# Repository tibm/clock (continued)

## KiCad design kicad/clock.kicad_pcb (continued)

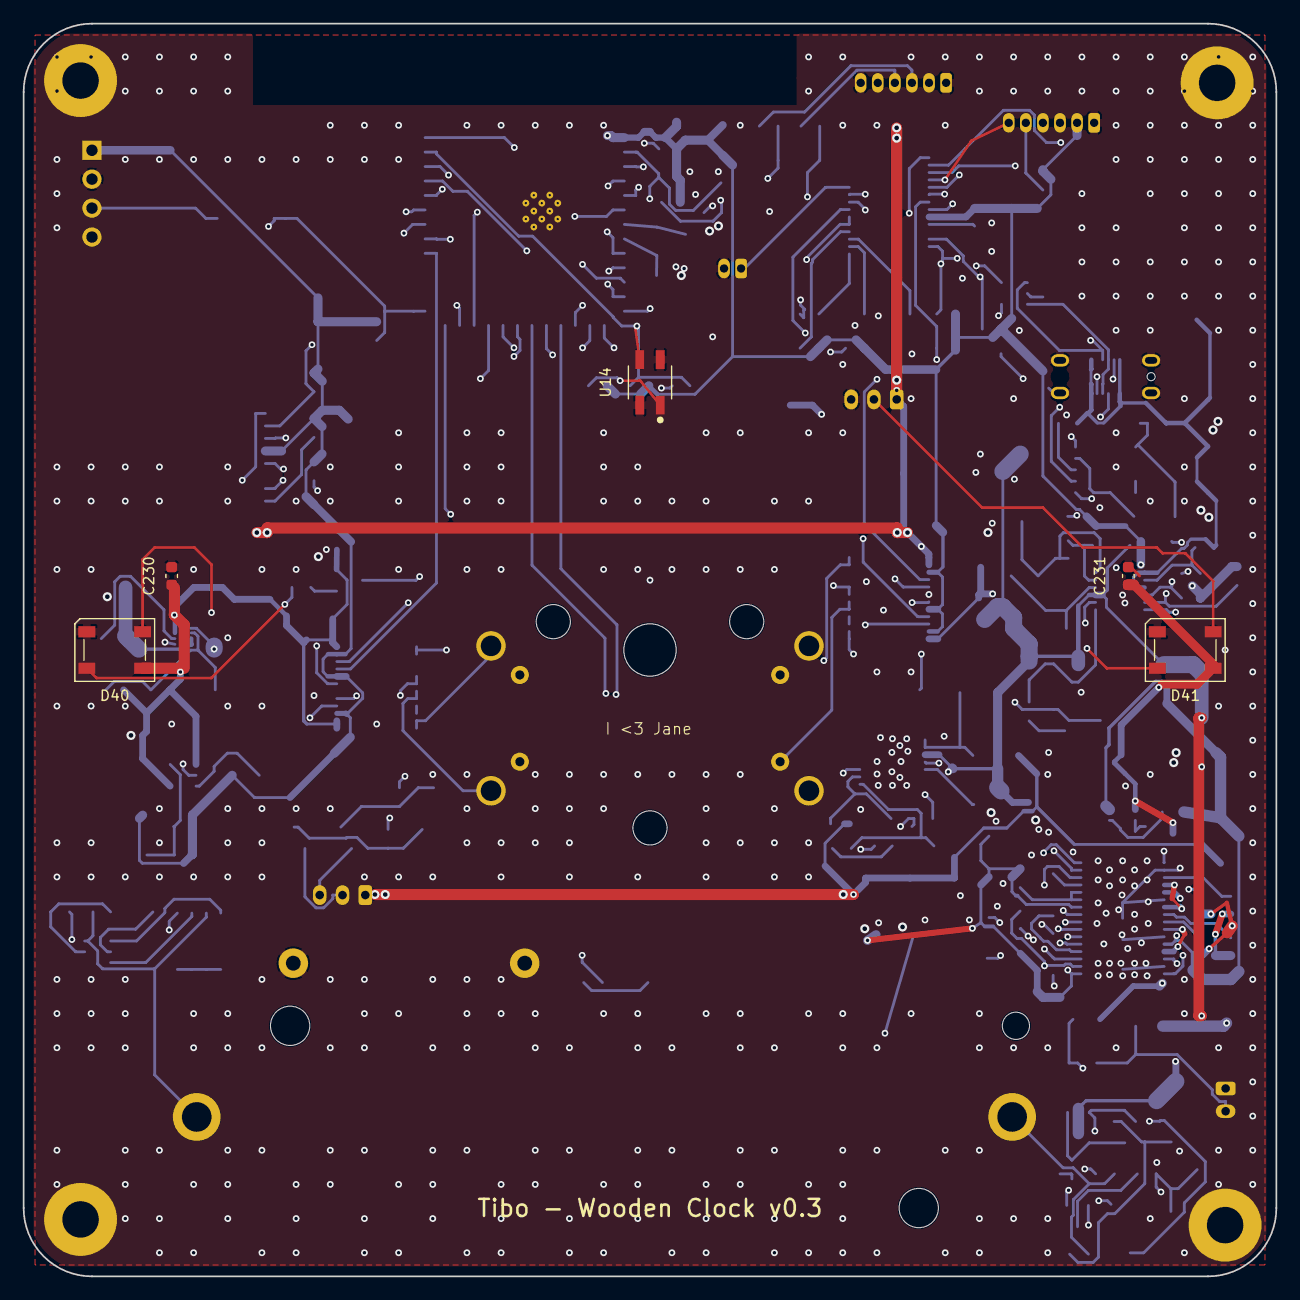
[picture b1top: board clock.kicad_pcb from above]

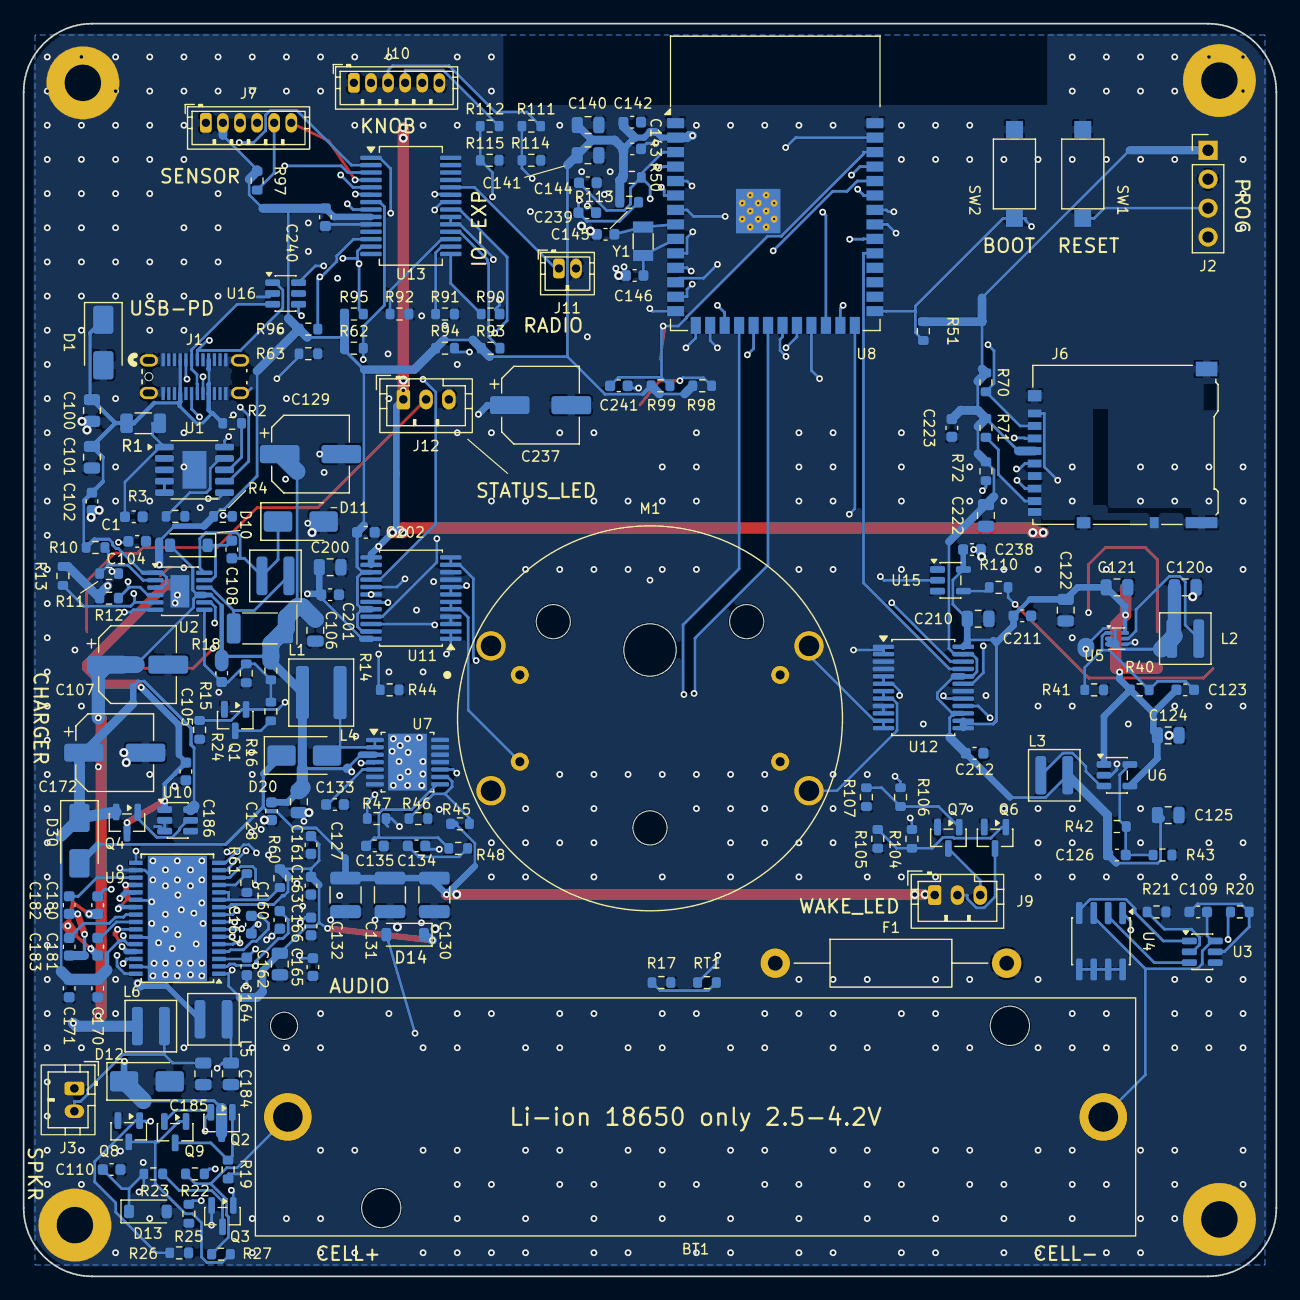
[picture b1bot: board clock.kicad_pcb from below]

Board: 4 copper layers, 110.0 x 110.0 mm, 187 parts (178 on the bottom side), 131 nets.

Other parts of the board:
H1, H2, H3, H4: MountingHole_3.2mm_M3_Pad

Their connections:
GND: H1.1, H2.1, H3.1, H4.1; also elsewhere on the board

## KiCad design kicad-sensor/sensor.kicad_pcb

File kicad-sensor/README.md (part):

# Wooden Smart Clock — sensor board (KiCad)

Small SMT daughterboard carrying the three off-board sensors, plugged into
**main-board J7** on a 6-way JST ZH harness. Open `sensor.kicad_pro`.

**The schematic is generated** by the Python in `gen/` (see *Regenerating*) —
edit the block files, not the `.kicad_sch`. **The PCB is not**: it has been
hand-placed and hand-routed since 2026-08-02, so `gen/pcb_build.py` refuses to
run and board changes are made in pcbnew + *Update PCB from Schematic* (F8).

**PCB: 30 × 16 mm, 4 layers, 1.6 mm — fully routed, `SENSE v0.2`
(2026-08-07).** Front face = the two sensors that must see the outside world
(TSL2591 window + BME688 vent); back face = the harness connector and the IMU.
Full rationale, floor plan, verification and the list of accepted deviations
in [`PCB_NOTES.md`](PCB_NOTES.md); the design review that drove v0.2 is in
[`REVIEW.md`](REVIEW.md).

This is "option **2b**" of [`../datasheet/README.md`](../datasheet/README.md) §15:
the same sensor set as the STEMMA-QT bring-up chain, on one board, at the same
I²C addresses, so firmware written against the breakouts runs unchanged.

| Ref | Part | Package | I²C | Datasheet |
|---|---|---|---|---|
| U1 | **BNO085** (CEVA/Hillcrest 9-axis fusion IMU, SH-2 on-chip) | LGA-28 5.2×3.8 *(land in `sensor.pretty`)* | **0x4A** (R3) / 0x4B (R4) | `../datasheet/sensor_imu_bno085.pdf` |
| U2 | **BME688** (gas/VOC + RH + pressure + temp) | LGA-8 3×3 | **0x77** (R10) / 0x76 (R11) | `../datasheet/sensor_env_bme688.pdf` + `…_bme68x_hsmi.pdf` |
| U3 | **TSL2591** (`TSL25911FN`, 188 µlx–88 klx ALS) | DFN-6 2×2 *(land in `sensor.pretty`)* | **0x29** (fixed) | `../datasheet/sensor_light_tsl2591.pdf` |
| Y1 | ABS07-32.768KHZ-T (BNO085 clock) | 3.2×1.5 SMD | — | `../datasheet/xtal_32k_abs07.pdf` |
| J1 | JST ZH **B6B-ZR** 1×06 | TH vertical | — | `../datasheet/connector_jst_zh.pdf` |

**Address straps are 10 kΩ, not 0 Ω** (v0.2). Exactly one of each pair is
fitted; the alternate carries a real `DNP` flag. Fitting both halves is the
assembly slip this layout invites, and through 0 Ω it would short the **main
board's** +3V3 rail to GND — on a daughterboard with no LED and no silk hint,
which is hours of debugging. Through 10 k the same slip costs 330 µA, the
clock still boots, and the part answers at a wrong-but-visible address.

No clash with the main board's own I²C devices (MCP23017 **0x20**, TAS5760M
**0x6C** — `SLEEP/ADR` strapped to GND, `kicad/gen/b_audio.py`; 0x6D is the
ADR-high alternate).

## J1 pinout — mirrors main-board J7 **1:1**

| Pin | Net | Main board (J7) | Sensor board |
|---|---|---|---|
| 1 | `GND` | GND | GND |
| 2 | `+3V3` | +3V3 | rails in — no regulator on this board |
| 3 | `I2C_SDA` | shared bus (4.7 k PU = R95) | U1.20 · U2.3 · U3.6 (+ R1 10 k) |
| 4 | `I2C_SCL` | shared bus (4.7 k PU = R96) | U1.19 · U2.4 · U3.1 (+ R2 10 k) |
| 5 | `SENSOR_INT` | MCU **IO42** IRQ, 10 k PU = R97 | **U1.14 `H_INTN` only** (push-pull, active low) |
| 6 | `ALS_INT` | **MCP23017 GPB3** (U13.4) | **U3.2 `INT`** (open drain, R12 10 k PU here — the only one on the net) |

Pin 6 was a spare wire when this board was designed; `kicad/REVIEW.md` #11
landed it on expander **GPB3**, so the ALS interrupt is live. Because the
pull-up lives only here, firmware must also set **`GPPU.3 = 1`** so GPB3 does
not float when this board is unplugged — `FIRMWARE.md` **R-BOARD-4**.

### ⚠ Harness polarity is a destructive fault

Both ends are ZHR-6 on the same pre-crimped cable and J1 mirrors J7 1:1, so a
cable loaded **backwards plugs in perfectly** — and J1.5 then receives J7.2
**+3V3 while this board's VDDIO is 0 V**. BNO08X abs max (Fig. 6-1) is
*"VDDIO + 0.3 V at any logic pin"*, series-limited only by the main board's
R97 10 k: **assume U1 ($13.57, the most expensive part on either board) is
destroyed.**

**This is not a hypothetical, and it is not only a mis-crimp: JST sells the
backwards cable as a catalogue part.** `A06ZR06ZR28H152`**`A`** is the
*Reversed* build (pin 1 ↔ pin 6, DigiKey 455-3027-ND) and
`A06ZR06ZR28H152`**`B`** is straight through (pin 1 ↔ pin 1, DigiKey
455-3039-ND) — one character apart, indistinguishable in the bag. The BOM has
always said `…B`; the cable that arrived for build #1 on **2026-09-08** was an
`…A`, and a continuity check is the only reason U1 survived it.

> **Standing procedure, before this harness ever goes into a powered board:**
> DMM on continuity, cable out of both boards, **pin 1 of one end to pin 1 of
> the other**. A beep on pin 1 ↔ pin 6 instead means re-pin it or bin it.

Worse, the main board's **J10** (knob) is the *same* ZH 1×06 header **13.5 mm
from J7**, with **+5 V on pin 2** — that mis-mate puts 5 V on `+3V3` and takes
out all three sensors at once (abs max: BNO085 VDDIO 3.63 V, TSL2591 3.8 V,
BME688 4.25 V).

Neither is keyed out, and **the connector is not going to change** — a 1×07
was proposed and rejected on 2026-08-08 ([`REVIEW.md`](REVIEW.md)). The guard
is marking, and it has to be followed: the main board carries **`SENSOR` and
`KNOB` on B.Silk** beside J7 and J10, so **label both harnesses to match, and
check the cable before first power-up.** The reversed-cable warning is also
printed on the schematic sheet next to J1 and on J10's BOM line, so it is in
front of whoever assembles the clock rather than only in this file.

## Design notes (all traceable to a datasheet line)

**BNO085 (`gen/b_imu.py`)** — follows the CEVA I²C reference design
(Fig. 1-11 and its notes 1-8):
- `PS1 = PS0 = 0` → I²C; `BOOTN` 10 k pull-up (R7) with test pad TP2 — pull it
  low at reset for the DFU bootloader.
- `CAP` (pin 9) → 100 nF to GND; VDD and VDDIO each get their own 100 nF
  (C3/C4) plus a 1 µF local bulk (C5) the reference omits — this board hangs
  off a long harness.
- **VDD and VDDIO share the 3V3 rail.** §6.3 demands VDD reach level *before
  or with* VDDIO; one rail satisfies that by construction.
- **32.768 kHz crystal** (Y1 + C7/C8 22 pF) with `CLKSEL0` **tied straight to
  GND — a bare wire, no strap resistor** (Fig. 1-8: *"0 or unconnected"*
  selects the crystal). The performance table (Fig. 6-14) is specified *only*
  for an external clock or crystal, so the internal RC is not used. Same ABS07
  part as the main board's RTC crystal (12.5 pF CL, ±20 ppm; CEVA asks
  50 ppm/12.5 pF).
- **`ENV_SCL`/`ENV_SDA` (pins 15/16) are pulled up although unused** — note 8:
  the SH-2 firmware probes that secondary bus at every reset. They are *not*
  tied to the host bus; on that bus the BNO085 is the master.
- **`NRST`**: J7 has no spare host line, so R6/C9 form a 10 k/100 nF power-on
  reset (TP1 to drive it by hand). It also guarantees the reset-sampled straps
  (BOOTN, PS1, PS0, CLKSEL0) are settled before release.
- **Deviation:** pin 18 `H_CSN` is unused in I²C mode and Fig. 1-11 leaves it
  open; R5 pulls it to VDDIO instead, so no CMOS input floats on a battery
  product. Harmless in every mode — `H_CSN` is not sampled at reset.

**BME688 (`gen/b_env.py`)** — §7.2 connection diagram (a):
- **`CSB` hard-tied to VDDIO.** §6.1: pull CSB low even once and the part
  latches into SPI until the next power-on reset and never answers I²C again.
- `SDO` must not float (§6.2). R10 (**10 k**) fitted → 0x77, matching the
  Adafruit 5046 breakout used for bring-up — which also uses 10 k; R11 (DNP)
  → 0x76, Bosch's own default. `SDO` is address-select only in I²C mode
  (Table 26) and is never driven, so a resistive strap is unambiguous.
- 100 nF on each supply (C10/C11).
- **Handling is the risk on this part, not wiring** — see *Assembly* below.

**TSL2591 (`gen/b_als.py`)** — "Application Information":
- **1 µF low-ESR at VDD** (C12), placed as close as possible to the pin.
- `INT` is open-drain → R12 10 k. Pin 4 is "NC — do not connect".

**Board level (`gen/b_host.py`)** — C1 10 µF + C2 100 nF at the connector
absorb the BME688 heater bursts (~18 mA peak) and the BNO085 turn-on so they
do not ride back up the single power wire. R1/R2 10 k parallel the main
board's 4.7 k to ≈3.2 k, inside the 2–4 kΩ window CEVA asks for (note 7) and
fast enough for 400 kHz over the harness; depopulate both to run on the 4.7 k
alone at 100 kHz. Two PWR_FLAGs declare the rails to ERC — nothing on this
board drives them.

## ⚠ Firmware constraint — do not poll the BNO085

Poll a BNO085 that has no data ready and it **stretches SCL until it does**
(§1.2.2.1). On this shared bus that stalls the BME688, the TSL2591 *and* the
main board's MCP23017 (knob, charger status, amp shutdown). Read it **only
after `SENSOR_INT` asserts**. `SENSOR_INT` carries nothing else, which is why
the TSL2591's interrupt went to the spare pin 6 instead.

Second, related, main-board item: CEVA says `H_INTN` "should be tied to a GPIO
**with wake capability**". `SENSOR_INT` lands on **IO42** (`../esp32.md`), which
is *not* an ESP32-S3 RTC GPIO (only IO0–IO21 are), so it can wake light sleep
but **not** `ext0`/`ext1` deep sleep. Fine if the clock never deep-sleeps with
tap-to-wake armed; otherwise move `SENSOR_INT` to an RTC-capable pin on the
next main-board revision. Not changed here — this board only presents the
signal on J1.5.

## Assembly

**All three sensors are leadless** (LGA-28 / LGA-8 / DFN-6) — this board
**cannot** be hand-soldered with an iron. Order it **fab-assembled**, or
reflow it yourself with a stencil + hotplate. The main board's
hand-solderable-only rule scopes the main PCB; this daughterboard is the
escape hatch that rule always assumed (`../datasheet/README.md` §15, path 2b).

**J1 is the only through-hole part**, so the board actually needs **three**
operations: reflow side 1, reflow side 2, then selective- or hand-solder J1.
Price that before committing — it is usually quoted per board, not per joint.
`B6B-ZR-SM4-TF` (same ZHR-6 housing, SMT with brass reinforcement) would
remove it at the cost of pull-out strength.

### ⚠ BME688 (U2) — put these in the fab package

A metal-oxide gas hotplate does not *fail* when mishandled; it reads a wrong
VOC baseline for ever, and a correctly-executed routine assembly process is
enough to do it. Datasheet §7.7 defers every rule to a separate **HSMI**
document, and Bosch publishes no BME688-specific one (checked 2026-08-07), so
the BME680 HSMI is filed as nearest-applicable — same LGA-8 3×3 package, same
Ø0.35 mm lid vent, same MOX element: **`../datasheet/sensor_env_bme68x_hsmi.pdf`**
(+ `…_bme68x_packaging.pdf`).

**These rules are in `U2`'s `Notes` field**, so they travel with the exported
BOM CSV to the assembly house instead of living only here — an assembler who
never opens this repo still gets them on the line they are quoting. Send
`../datasheet/sensor_env_bme68x_hsmi.pdf` with the fab package and get the
≥ 50 µm solder height agreed **before** the run: it is a stencil-thickness
decision, not something that can be fixed afterwards.

| Rule | |
|---|---|
| **MSL 1** | no bake needed |
| **Peak reflow 260 °C, 20–40 s**, **≤ 3 cycles** | this board is double-sided, so U2 already sees two |
| **≥ 50 µm solder height after reflow** | a **stencil-thickness** decision, not a layout one — it is what mechanically decouples the die from the board |
| **Cover the vent** with a silicone-free layer for any cleaning / board wash | or specify no-clean and no wash |
| **No siloxanes** — coatings, adhesives, gloves, packaging | permanent VOC poisoning |
| No conformal coat, no underfill, no ultrasonic welding, nothing sharp in the vent, no rear-side handling | |

## Custom footprints (`sensor.pretty`, fp-lib-table nickname `sensor`)

| Footprint | Part | Source |
|---|---|---|
| `AMS_TSL25911FN_ALSWindow` | U3 | **Fork of stock `OptoDevice:AMS_TSL25911FN`** (v0.2). Identical pads, courtyard, F.Fab and Cmts.User; the **F.Silk package outline is removed** and the pin-1 marker moved outboard. The stock silk crosses the enclosure's Ø4.0 mm optical window 1.31 mm from the photodiode, and white silk that close under a window is a diffuse reflector. Forked rather than hand-edited on the board so *Update Footprints from Library* cannot put it back — and so `kicad-cli pcb drc` stays at 0 (a hand-edited instance reports `lib_footprint_mismatch` for ever). Its `(model …)` points straight at `3d/AMS_TSL25911FN.step`, the override the stock footprint needed anyway. |
| `CEVA_BNO085_LGA-28_5.2x3.8mm_P0.5mm` | U1 | **Vendor (SnapEDA) land, verified against BNO08X datasheet Fig. 7-2** — measured land extents **5.2000 × 3.8000 mm**, i.e. exactly the drawing. Pad centres ±1.5625 (10-pad rows) and ±2.3125 (4-pad ends), pads 0.25 × 0.675 / 0.575 × 0.25. Cleaned on import: SnapEDA's per-pad `solder_mask_margin 0.102` **removed** (at 0.5 mm pitch it left a 0.046 mm mask web — below any fab's minimum dam, so the mask would have silently ganged; board default gives 0.25 mm), pin-1 silk dot grown from Ø0.2 to Ø0.42 (was under the 0.15 mm silk minimum), `3d/BNO085.step` linked, renamed to house style, resaved through `kicad-cli fp upgrade`. Pad numbering/arrangement cross-checked against the drawing and against KiCad's stock generic pattern — identical. |

KiCad's stock `Package_LGA:LGA-28_5.2x3.8mm_P0.5mm` is a **generic IPC** land: same
numbering and arrangement, but ~0.10 mm (row pads) / 0.125 mm (end pads) of extra toe
per side → 4.00 × 5.45 instead of 3.80 × 5.20. Not wrong, just unverified against this
part; the vendor land above is used instead so nothing needs checking before fab.

## Custom symbol (`gen/sensor_custom.kicad_sym`)

`BNO085` — KiCad has no BNO08x symbol (`Sensor_Motion:BNO055` is the same
*package* with a completely different pinout). Pins are grouped by function:
host I²C and the strapped pins on the left, clock / CAP / ENV bus on the
right, supplies top, grounds bottom, and the nine `RESV_NC` pads kept visible
so every pad is accounted for. The other two sensors use stock symbols
verbatim — `Sensor:BME680` with the value overridden to **BME688** (identical
pin table per BME688 Table 26 and identical LGA-8 3×3 P0.8 clockwise package)
and `Sensor_Optical:TSL25911FN`.

## Before fab

1. ~~LGA-28 land pattern~~ — **closed 2026-07-29**: U1 now uses the vendor land in
   `sensor.pretty`, measured against datasheet Fig. 7-2 (see above). The BME688
   (`Bosch_LGA-8_3x3mm_P0.8mm_ClockwisePinNumbering`) and TSL2591 (stock
   `OptoDevice:AMS_TSL25911FN`, forked here only to trim its silk) footprints
   are part-specific KiCad libs generated from those datasheets, so they need
   no separate check.
2. **Harness polarity** — 1:1, not reversed. Label both cables; J10 on the
   main board is the same connector 13.5 mm away (above).
3. ~~Placement~~ — **closed 2026-07-30**, revised 2026-08-07, see
   [`PCB_NOTES.md`](PCB_NOTES.md): U2 has the far corner, a 4-layer pour
   keepout, a clear back side and a Ø5.2 mm vent marked on `User.Drawings`; U3
   has a Ø4.0 mm window with nothing but its own pads inside it, on copper or
   silk; U1 sits 0.038 mm off the line between the two M2 screws. Still on the
   enclosure side: keep the vent away from the amp/LED/battery heat and the
   ALS off-axis from the dial LEDs, and **use nylon or brass M2 screws** —
   steel next to the magnetometer is a permanent hard-iron offset.
4. ~~Route it~~ — **closed 2026-08-02**: 193 segments, 30 vias, 4 GND pours.
5. **BME688 handling** — the HSMI rules above go in the fab package with the
   Gerbers, and the ≥ 50 µm solder height is a stencil decision the assembler
   has to agree to *before* the run.

## Validation (2026-08-07, v0.2)

- `kicad-cli sch erc sensor.kicad_sch` → **0 violations**, and *"Global label
  only appears once in the schematic"* is **no longer suppressed** — on a
  single-sheet design where every inter-block connection is a global label,
  that is the check that catches a typo'd label name.
- `kicad-cli pcb drc --severity-all` → **0 violations, 0 unconnected items, 0
  schematic-parity issues.**
- `gen/pcb_check.py`, which re-checks the *saved* file independently (loads the
  board, re-exports the netlist, re-derives the outline from Edge.Cuts) →
  **33/33**. It was re-baselined for v0.2: it now judges part clearance on
  **pad-to-pad copper** (≥ 0.60 mm everywhere) rather than on courtyards,
  checks mounting holes at the **hole wall** rather than at the screw-head
  keepout, and adds three checks — every filled zone island is stitched, no
  F.Silk inside the optical window, and **PCB title block == schematic title
  block == the `SENSE v0.2` silk legend**. Details in
  [`PCB_NOTES.md`](PCB_NOTES.md).
- BOM: all 29 BOM parts carry MPN/Manufacturer/Package/Description, board
  fields identical to the schematic's, and the DNP / off-BOM sets agree
  between the two files. `gen/stamp_bom.py` re-run is a no-op (idempotent) and
  both files round-trip byte-identically through KiCad's own writers.
- `gen/build.py` lint: no dangling wires, no body overlaps, no wires through
  symbols; junctions placed by eeschema's own rules so a GUI re-save is a
  no-op. The sheet is normalised through `kicad-cli sch upgrade`, so opening
  and saving in eeschema produces zero diff.
- Netlist spot-checked pin-by-pin against the three datasheets (every
  `RESV_NC` and the TSL2591 `NC` land on their own unconnected nets).

## BOM part data (`gen/parts_db.py` + `gen/stamp_bom.py`, 2026-08-01)

The generators only emit Value + Footprint, which is not a BOM: this board is
**ordered fab-assembled**, so every line has to be unambiguous to an assembly
house (`MPN` + `Package`) and the parts that must *not* be fitted have to say
so in a field, not in a value string.

```
cd gen && python3 stamp_bom.py          # --dry-run to preview
```

splices **MPN / Manufacturer / Package / Description / Notes** into *both*
`sensor.kicad_sch` (eeschema + `kicad-cli` BOMs) and `sensor.kicad_pcb` (the
PCBWay plug-in reads *footprint* fields) — in place, no regeneration, so hand
DRC fixes survive — then sets two kinds of flag and hands both files back to
KiCad's own serializers (`kicad-cli sch upgrade` + `gen/pcb_canon.py`) so they
stay byte-identical to a GUI save. Idempotent; fails loudly on a part that is
missing from the db. **Re-run it after every `build.py` rebuild** — the
schematic generator writes its file from scratch and drops the fields.

- **DNP** (`parts_db.DNP`) → `(dnp yes)` on the symbol + the `dnp` footprint
  attribute. **R4 and R11 are the alternate I²C-address straps**: only their
  *value strings* said "(DNP)", so a BOM taken before 2026-08-01 told the
  assembler to fit them — and R3+R4 or R10+R11 fitted together tied +3V3 to
  GND through 0 Ω. They now export with KiCad's `DNP` column set **and** the
  straps are **10 k** (v0.2), so the flag is the guard and the value is the
  fail-safe under it: the same slip now costs 330 µA instead of the main
  board's 3.3 V rail.
- **Not a part** (`parts_db.EXCLUDE_FROM_BOM`) → `(in_bom no)` +
  `(in_pos_files no)` on TP1/TP2, matching the `exclude_from_bom` their
  footprints already carried, so the schematic-side and PCB-side BOMs agree
  (and "Update PCB from Schematic" can't put the test pads back).

Part data: the three sensors + the crystal + J1 are local to
`gen/parts_db.py`; the **generic passives are imported from the main board's
`../../kicad/gen/parts_db.py`**, so both boards order the same physical 0603 /
0805 parts. Per-reference data never falls through to the main board's table —
J1/U1/U2/U3/Y1 exist there too and mean different parts. DigiKey status/price
re-verified 2026-08-01 (BNO085 1888-1006-1-ND $13.57 · BME688 828-BME688CT-ND
$8.99 — `../datasheet/README.md` §12's ~$5 is the reel price · TSL25911FN
TSL25911FNTR-ND $1.74; all Active) and J1 re-checked 2026-08-07
(455-B6B-ZR-ND, $0.24, 9,478 pcs).

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
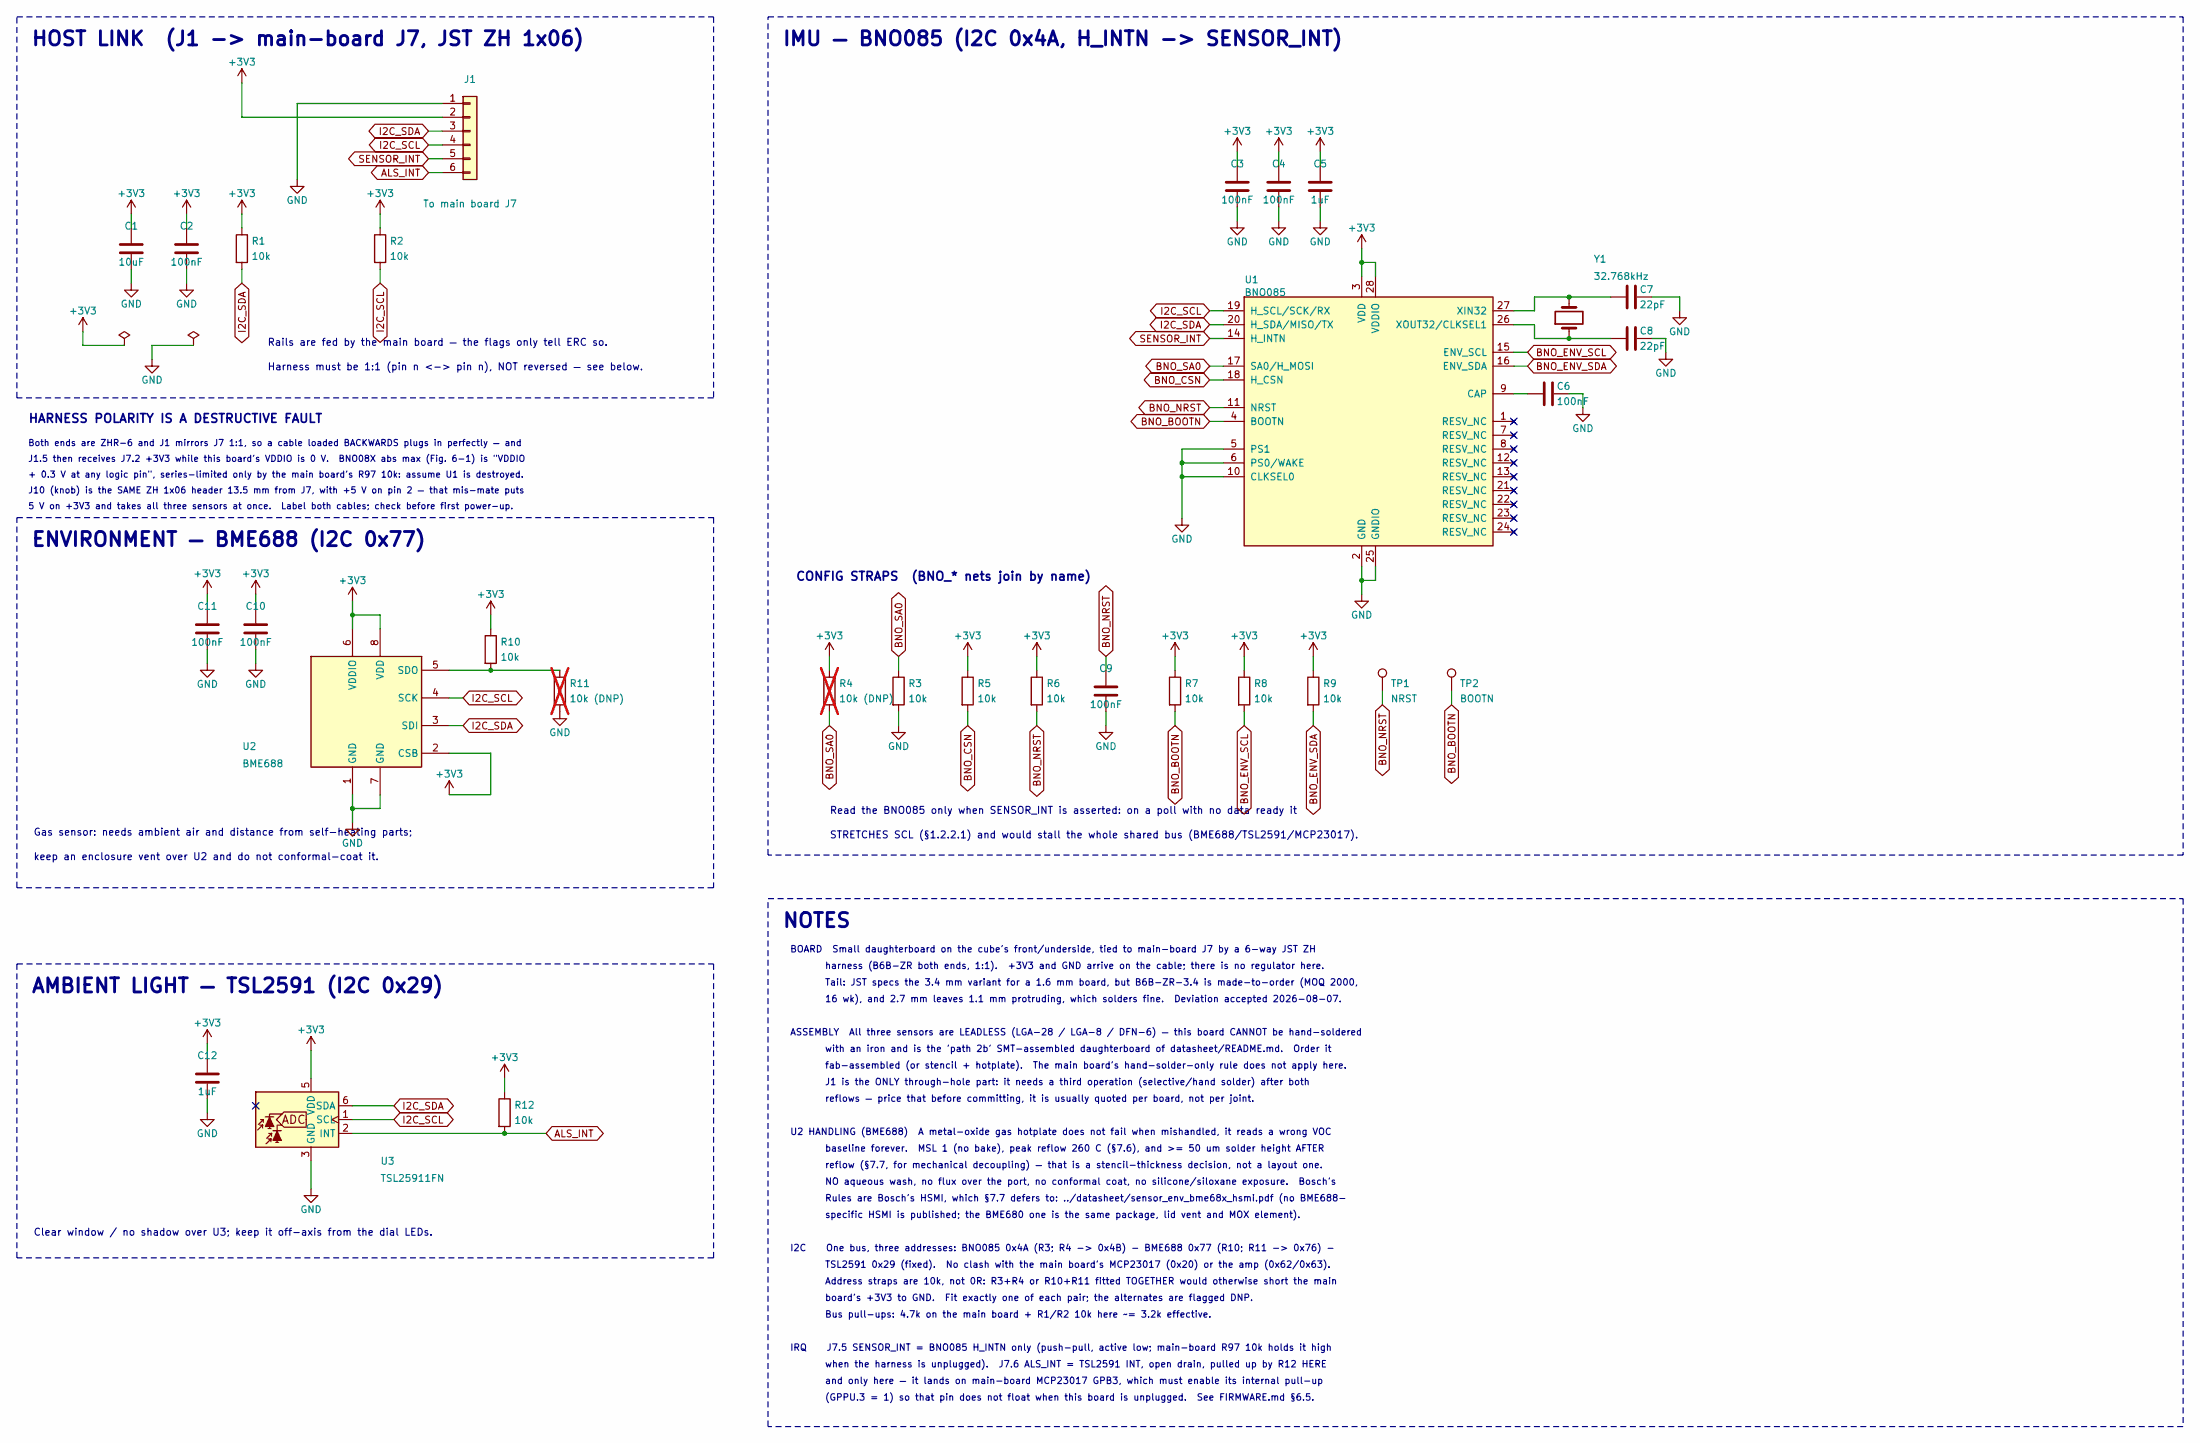
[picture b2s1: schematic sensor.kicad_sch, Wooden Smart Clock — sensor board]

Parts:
C1: 10uF; C_0805_2012Metric; MPN CL21A106KAYNNNE
C2, C3, C4, C6, C9, C10, C11: 100nF; C_0603_1608Metric; MPN CL10B104KB8NNNC
C5, C12: 1uF; C_0603_1608Metric; MPN CL10B105KA8NNNC
C7, C8: 22pF; C_0603_1608Metric; MPN CL10C220JB8NNNC
J1: To main board J7; JST_ZH_B6B-ZR_1x06_P1.50mm_Vertical; MPN B6B-ZR(LF)(SN)
R1, R2, R3, R5, R6, R7, R8, R9, R10, R12: 10k; R_0603_1608Metric; MPN RC0603FR-0710KL
R4, R11: 10k (DNP); R_0603_1608Metric; MPN RC0603FR-0710KL; not fitted
TP1: NRST; TestPoint_Pad_D1.0mm
TP2: BOOTN; TestPoint_Pad_D1.0mm
U1: BNO085; CEVA_BNO085_LGA-28_5.2x3.8mm_P0.5mm; MPN BNO085
U2: BME688; Bosch_LGA-8_3x3mm_P0.8mm_ClockwisePinNumbering; MPN BME688
U3: TSL25911FN; AMS_TSL25911FN_ALSWindow; MPN TSL25911FN
Y1: 32.768kHz; Crystal_SMD_3215-2Pin_3.2x1.5mm; MPN ABS07-32.768KHZ-T

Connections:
+3V3: C1.1, C2.1, C3.1, C4.1, C5.1, C10.1, C11.1, C12.1, J1.2, R1.1, R2.1, R4.1, R5.1, R6.1, R7.1, R8.1, R9.1, R10.1, R12.1, U1.3 (VDD), U1.28 (VDDIO), U2.2 (CSB), U2.6 (VDDIO), U2.8 (VDD), U3.5 (VDD)
ALS_INT: J1.6, R12.2, U3.2 (INT)
BNO_BOOTN: R7.2, TP2.1, U1.4 (BOOTN)
BNO_CSN: R5.2, U1.18 (H_CSN)
BNO_ENV_SCL: R8.2, U1.15 (ENV_SCL)
BNO_ENV_SDA: R9.2, U1.16 (ENV_SDA)
BNO_NRST: C9.1, R6.2, TP1.1, U1.11 (NRST)
BNO_SA0: R3.1, R4.2, U1.17 (SA0/H_MOSI)
GND: C1.2, C2.2, C3.2, C4.2, C5.2, C6.2, C7.2, C8.2, C9.2, C10.2, C11.2, C12.2, J1.1, R3.2, R11.2, U1.2 (GND), U1.5 (PS1), U1.6 (PS0/WAKE), U1.10 (CLKSEL0), U1.25 (GNDIO), U2.1 (GND), U2.7 (GND), U3.3 (GND)
I2C_SCL: J1.4, R2.2, U1.19 (H_SCL/SCK/RX), U2.4 (SCK), U3.1 (SCL)
I2C_SDA: J1.3, R1.2, U1.20 (H_SDA/MISO/TX), U2.3 (SDI), U3.6 (SDA)
unnamed: C6.1, U1.9 (CAP)
unnamed: C7.1, U1.27 (XIN32), Y1.2
unnamed: C8.1, U1.26 (XOUT32/CLKSEL1), Y1.1
unnamed: R10.2, R11.1, U2.5 (SDO)
SENSOR_INT: J1.5, U1.14 (H_INTN)

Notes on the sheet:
STRETCHES SCL (§1.2.2.1) and would stall the whole shared bus (BME688/TSL2591/MCP23017).
ENVIRONMENT — BME688 (I2C 0x77)
Rails are fed by the main board — the flags only tell ERC so.
J1.5 then receives J7.2 +3V3 while this board's VDDIO is 0 V. BNO08X abs max (Fig. 6-1) is "VDDIO
Rules are Bosch's HSMI, which §7.7 defers to: ../datasheet/sensor_env_bme68x_hsmi.pdf (no BME688-
ASSEMBLY All three sensors are LEADLESS (LGA-28 / LGA-8 / DFN-6) — this board CANNOT be hand-soldered
reflows — price that before committing, it is usually quoted per board, not per joint.
fab-assembled (or stencil + hotplate). The main board's hand-solder-only rule does not apply here.
5 V on +3V3 and takes all three sensors at once. Label both cables; check before first power-up.
BOARD Small daughterboard on the cube's front/underside, tied to main-board J7 by a 6-way JST ZH
HARNESS POLARITY IS A DESTRUCTIVE FAULT
baseline forever. MSL 1 (no bake), peak reflow 260 C (§7.6), and >= 50 um solder height AFTER
Read the BNO085 only when SENSOR_INT is asserted: on a poll with no data ready it
16 wk), and 2.7 mm leaves 1.1 mm protruding, which solders fine. Deviation accepted 2026-08-07.
AMBIENT LIGHT — TSL2591 (I2C 0x29)
Harness must be 1:1 (pin n <-> pin n), NOT reversed — see below.
TSL2591 0x29 (fixed). No clash with the main board's MCP23017 (0x20) or the amp (0x62/0x63).
I2C One bus, three addresses: BNO085 0x4A (R3; R4 -> 0x4B) - BME688 0x77 (R10; R11 -> 0x76) -
IMU — BNO085 (I2C 0x4A, H_INTN -> SENSOR_INT)
specific HSMI is published; the BME680 one is the same package, lid vent and MOX element).
U2 HANDLING (BME688) A metal-oxide gas hotplate does not fail when mishandled, it reads a wrong VOC
J1 is the ONLY through-hole part: it needs a third operation (selective/hand solder) after both
Address straps are 10k, not 0R: R3+R4 or R10+R11 fitted TOGETHER would otherwise short the main
harness (B6B-ZR both ends, 1:1). +3V3 and GND arrive on the cable; there is no regulator here.
Tail: JST specs the 3.4 mm variant for a 1.6 mm board, but B6B-ZR-3.4 is made-to-order (MOQ 2000,
IRQ J7.5 SENSOR_INT = BNO085 H_INTN only (push-pull, active low; main-board R97 10k holds it high
Gas sensor: needs ambient air and distance from self-heating parts;
keep an enclosure vent over U2 and do not conformal-coat it.
HOST LINK (J1 -> main-board J7, JST ZH 1x06)
with an iron and is the 'path 2b' SMT-assembled daughterboard of datasheet/README.md. Order it
NO aqueous wash, no flux over the port, no conformal coat, no silicone/siloxane exposure. Bosch's
Clear window / no shadow over U3; keep it off-axis from the dial LEDs.
Both ends are ZHR-6 and J1 mirrors J7 1:1, so a cable loaded BACKWARDS plugs in perfectly — and
CONFIG STRAPS (BNO_* nets join by name)
(GPPU.3 = 1) so that pin does not float when this board is unplugged. See FIRMWARE.md §6.5.
+ 0.3 V at any logic pin", series-limited only by the main board's R97 10k: assume U1 is destroyed.
NOTES
and only here — it lands on main-board MCP23017 GPB3, which must enable its internal pull-up
J10 (knob) is the SAME ZH 1x06 header 13.5 mm from J7, with +5 V on pin 2 — that mis-mate puts
when the harness is unplugged). J7.6 ALS_INT = TSL2591 INT, open drain, pulled up by R12 HERE

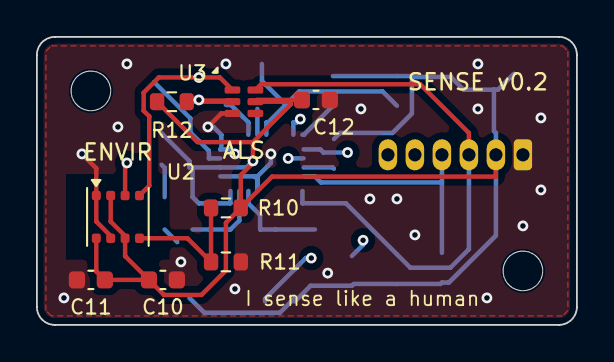
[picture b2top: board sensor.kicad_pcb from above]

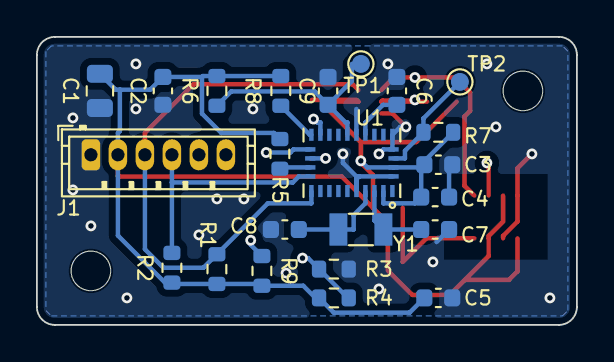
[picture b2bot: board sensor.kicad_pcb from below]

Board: 4 copper layers, 30.0 x 16.0 mm, 33 parts (23 on the bottom side), 16 nets.

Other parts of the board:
H1, H2: MountingHole_2.2mm_M2

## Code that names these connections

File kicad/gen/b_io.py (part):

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    s.power_at(505.46, 251.46, "GND")
    s.pw(J7, "2", ("x", 510.54), ("y", 246.38))
    s.power_at(510.54, 246.38, "+3V3")
    s.glabel(J7, "3", "I2C_SDA")
    s.glabel(J7, "4", "I2C_SCL")
    s.glabel(J7, "5", "SENSOR_INT")
    # pin 6 is NOT spare: the sensor board drives ALS_INT (TSL2591 INT, pulled
    # up there by its R12) onto it.  Land it on the expander's free GPB3 so the
    # light sensor can interrupt instead of being polled.  [REVIEW.md #11]
    s.glabel(J7, "6", "ALS_INT")
    # SENSOR_INT pull-up (INT lines are open-drain)
    R97 = s.R("R97", 541.02, 254.00, "10k")
    s.rail(R97, "1", "+3V3", rise=0)
    s.pw(R97, "2", ("dy", 2.54))
    s.glabel_at("SENSOR_INT", 541.02, 260.35, 270)

    # QRE1113GR (SMD) reflective homing -> HOME_OPTO (MCU ADC IO2)
    U14 = s.comp("U14", "Sensor_Proximity:QRE1113", 443.23, 256.54,
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    s.pw(U14, "3", ("x", 466.09))                     # collector node
    C241 = s.C("C241", 461.01, 257.81, "100nF")
    s.gnd(C241, "2", drop=0)
    s.glabel_at("HOME_OPTO", 466.09, 254.00, 0)
    s.gnd(U14, "4", via=2.54)                         # emitter
    s.text("QRE1113GR faces reflective tabs on the hand hubs (no magnets).", 486.41, 297, size=1.3)
    s.text("Sensor breakouts carry their own I2C pull-ups.", 486.41, 301.5, size=1.3)
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    s.nc(U13, "11")
    s.nc(U13, "14")
    s.nc(U13, "28")                                    # GPA7 spare
    s.glabel(U13, "8", "CELL_TEST")                    # GPB7: cell-detect (b_charger)

    # I2C bus stubs + main-board pull-ups
    s.pw(U13, "12", ("x", 450.85))
    s.glabel_at("I2C_SCL", 450.85, 449.58, 180)
    s.pw(U13, "13", ("x", 440.69))
    s.glabel_at("I2C_SDA", 440.69, 452.12, 180)
    R96 = s.R("R96", 469.90, 443.23, "4.7k")
    s.rail(R96, "1", "+3V3", rise=0)
    s.pw(R96, "2", ("y", 449.58))
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        s.pw(U13, pin, ("x", tx), ("pin", r, "1"))
        s.gnd(r, "2", drop=0)

    # GPA fan-out: labels for far nets.  SPK_SD carries no label of its own
    # here -- GPA0 runs right and meets R63's stub, and the single SPK_SD
    # label sits at that junction (one label, not two facing each other).
    s.pw(U13, "21", ("x", 571.50))
    s.glabel(U13, "22", "STEP_STBY")
    s.glabel(U13, "23", "BOOST12_EN")

    # GPA3..GPA6 freed 2026-07-19 (BTN1-3 dropped, ENC_SW moved to the host
    # IO17). GPA3 -> J11: rear radio-disable toggle (MCP internal PU + IOC;
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        s.nc(U13, p)

    # GPB fan-out labels (GPB3 freed 2026-07-19: LCD_DISP gone with the display)
    for pin, name in [("1", "PD_PG"), ("2", "CHRG"), ("3", "FAULT"),
                      ("5", "FULLCHG_EN"), ("6", "VBAT_DIV_EN")]:
        s.glabel(U13, pin, name)
    s.glabel(U13, "4", "ALS_INT")                      # GPB3 = TSL2591 INT (J7.6)
    # SPK_FAULT (GPB6): run right, open-drain pull-up R62 hangs on it
    s.pw(U13, "7", ("x", 535.94), ("dx", 2.54))
    s.glabel_at("SPK_FAULT", 538.48, 487.68, 0)
    R62 = s.R("R62", 535.94, 480.06, "10k")
    s.pw(R62, "2", ("y", 487.68))
    s.pw(R62, "1", ("dy", -1.27))
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    R63 = s.R("R63", 556.26, 481.33, "100k")
    s.pw(R63, "1", ("x", 571.50), ("y", 449.58))   # pin1 -> the GPA0 run
    s.w((571.50, 449.58), (577.85, 449.58))
    s.glabel_at("SPK_SD", 577.85, 449.58, 0)
    s.gnd(R63, "2", drop=0)

    # ---- knob connector: Bourns EM14A0D-C24-L064S optical encoder (5 V,
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    # label on a short stub left of R113 pin 2 so it clears the pin-2
    # junction (hand-moved in eeschema 2026-07-21)
    s.w(r113_2, (501.65, r113_2[1]))
    s.glabel_at("ENC_SW", 501.65, r113_2[1], 180)
    C239 = s.C("C239", 537.21, 556.26, "100nF")   # pin 1 taps the row
    s.pw(C239, "1", ("y", r113_2[1]))
    s.gnd(C239, "2", drop=0)
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
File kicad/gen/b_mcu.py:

"""Block: MCU — ESP32-S3-WROOM-1-N8R8 (custom functionally-grouped symbol).
Straps (EN/IO0 + buttons + PROG header), XTAL32K, decoupling, and labels for
bus/far nets. SPI/I2S/motor/encoder/INT wires are drawn by their peripheral
blocks via s.parts["U8"].
"""
U = 2.54


def build(s):
    s.frame(405, 40, 595, 215, "MCU — ESP32-S3-WROOM-1-N8R8 (Wi-Fi + BLE, native USB-JTAG)")

    U8 = s.comp("U8", "clock:ESP32S3_CLOCK", 525.78, 139.70,
                value="ESP32-S3-WROOM-1-N8R8",
                footprint="RF_Module:ESP32-S3-WROOM-1",
                refpos=(505.46, 97.79, "left"), valpos=(505.46, 190.50, "left"))
    s.parts["U8"] = U8

    # ---- 3V3 + decoupling (10u + 22u + 100n x2) ----
    s.w((445.77, 92.71), (525.78, 92.71), (525.78, 100.33))   # to the 3V3 pin
    s.power_at(455.93, 87.63, "+3V3")
    s.w((455.93, 87.63), (455.93, 92.71))
    for ref, x, v, fp in [("C140", 445.77, "10uF", "C0805"),
                          ("C141", 453.39, "22uF", "C0805"),
                          ("C142", 461.01, "100nF", "C0603"),
                          ("C143", 468.63, "100nF", "C0603")]:
        c = s.C(ref, x, 96.52, v, fp=fp)
        s.gnd(c, "2", drop=0, show_value=False)
    # ---- GND pins ----
    s.w((523.24, 179.07), (528.32, 179.07))
    s.w((525.78, 179.07), (525.78, 181.61))
    s.power_at(525.78, 181.61, "GND")

    # ---- EN strap: 10k PU + 1uF + RESET button + PROG header ----
    s.pw(U8, "3", ("x", 441.96))                     # EN row wire
    R50 = s.R("R50", 490.22, 102.87, "10k")
    s.rail(R50, "1", "+3V3", rise=0)
    s.jpin(R50, "2")
    C144 = s.C("C144", 474.98, 110.49, "1uF")
    s.pw(C144, "1", ("y", 106.68))
    s.gnd(C144, "2", drop=0)
    SW1 = s.comp("SW1", "Switch:SW_Push", 461.01, 114.30, value="RESET",
                 footprint="Button_Switch_SMD:SW_SPST_CK_RS282G05A3")
    s.pw(SW1, "2", ("y", 106.68))
    s.gnd(SW1, "1", via=-2.54)
    # ---- IO0 strap: 10k PU + BOOT button (PU left of the EN row) ----
    s.pw(U8, "27", ("x", 435.61))                    # IO0 row wire
    R51 = s.R("R51", 435.61, 105.41, "10k")
    s.rail(R51, "1", "+3V3", rise=0)
    SW2 = s.comp("SW2", "Switch:SW_Push", 463.55, 125.73, value="BOOT",
                 footprint="Button_Switch_SMD:SW_SPST_CK_RS282G05A3")
    s.pw(SW2, "2", ("x", 468.63), ("y", 109.22))
    s.gnd(SW2, "1", via=0, drop=3.81)
    # PROG header: 3V3 / GND / EN / IO0
    J2 = s.comp("J2", "Connector_Generic:Conn_01x04", 421.64, 116.84,
                mirror="y", value="PROG",
                footprint="Connector_PinHeader_2.54mm:PinHeader_1x04_P2.54mm_Vertical",
                refpos=(429.26, 109.22, None), valpos=(429.26, 127.00, None))
    s.rail(J2, "1", "+3V3", rise=2.54)
    s.gnd(J2, "2", via=2.54, drop=7.62)
    s.pw(J2, "3", ("x", 441.96), ("y", 106.68))      # EN
    s.pw(J2, "4", ("x", 444.50), ("y", 109.22))      # IO0

    # ---- 32.768 kHz crystal ----
    Y1 = s.comp("Y1", "Device:Crystal", 490.22, 123.19, rot=90, value="32.768kHz",
                footprint="Crystal:Crystal_SMD_3215-2Pin_3.2x1.5mm",
                refpos=(492.76, 123.19, "left"), valpos=(488.19, 123.19, "right"))
    s.pw(U8, "8", ("x", 494.03), ("y", 119.38), ("px", Y1, "2"))
    s.pw(U8, "9", ("x", 494.03), ("y", 127.00), ("px", Y1, "1"))
    C145 = s.C("C145", 480.06, 119.38, "18pF", rot=90)
    s.route(C145, "2", Y1, "2", "H")
    s.gnd(C145, "1", drop=1.27)
    C146 = s.C("C146", 477.52, 127.00, "18pF", rot=90)
    s.route(C146, "2", Y1, "1", "H")
    s.gnd(C146, "1", via=0, drop=3.81)

    # ---- left-side nets (labels) ----
    s.glabel(U8, "13", "USB_DM")
    s.glabel(U8, "14", "USB_DP")
    s.glabel(U8, "39", "VBAT_SENSE")
    s.glabel(U8, "38", "HOME_OPTO")
    s.glabel(U8, "35", "SENSOR_INT")
    for p in ("28", "29", "30"):                     # PSRAM-reserved pads
        s.nc(U8, p)

    # ---- right-side nets (labels; buses are wired by peripheral blocks) ----
    s.glabel(U8, "12", "I2C_SDA")
    s.glabel(U8, "17", "I2C_SCL")
    s.glabel(U8, "10", "ENC_SW")
    s.glabel(U8, "7", "NEOPIX_DATA")
    s.glabel(U8, "26", "WAKE_WARM_PWM")
    s.glabel(U8, "16", "WAKE_COOL_PWM")

    s.text("IO35-37 reserved by the octal PSRAM (N8R8).   Straps: IO0 high; IO45/46 low via", 410, 48, size=1.3)
    s.text("their wake gate nets + internal PD; IO3 internal.  Flash+console+JTAG = USB-CDC (IO19/20).", 410, 53, size=1.3)

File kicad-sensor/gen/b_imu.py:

"""Block: IMU — BNO085 (CEVA/Hillcrest 9-axis fusion, I2C @ 0x4A).

Wired per the datasheet's own I2C reference design (Fig. 1-11 + notes 1-8,
§1.2.1/§1.2.2), with three deliberate deviations, all called out below:
  * pin 18 H_CSN is pulled to VDDIO instead of being left floating,
  * CLKSEL0 is tied straight to GND -- a bare wire, no strap resistor --
    instead of being driven by a host GPIO (Fig. 1-8: "0 or unconnected"
    selects the crystal),
  * NRST gets an RC power-on reset because J7 has no spare host line.

Config straps live in their own row under the symbol and reach the pins by
name (BNO_* labels) — the same style CEVA's reference schematic uses.
"""


def build(s):
    s.frame(150, 26, 410, 180, "IMU — BNO085 (I2C 0x4A, H_INTN -> SENSOR_INT)")

    # Footprint is the vendor (SnapEDA) land, not KiCad's generic
    # Package_LGA:LGA-28_5.2x3.8mm_P0.5mm — the stock one is an IPC pattern whose
    # pads sit 0.10/0.125 mm further out per side; this one measures exactly the
    # 5.2 x 3.8 of datasheet Fig. 7-2.  See ../sensor.pretty + README.
    U1 = s.comp("U1", "sensor:BNO085", 260.35, 100.33, value="BNO085",
                footprint="sensor:CEVA_BNO085_LGA-28_5.2x3.8mm_P0.5mm")

    # ---------------- supplies ----------------
    # VDD (sensors) and VDDIO (core/IO) share the 3V3 rail: §6.3 requires VDD
    # to reach level before or WITH VDDIO — one rail satisfies that by
    # construction.
    s.pw(U1, "3", ("dy", -5.08))
    s.power_at(259.08, 68.58, "+3V3")
    s.pw(U1, "28", ("dy", -2.54), ("x", 259.08))
    s.pw(U1, "2", ("dy", 5.08))
    s.power_at(259.08, 132.08, "GND")
    s.pw(U1, "25", ("dy", 2.54), ("x", 259.08))

    # C3/C4 = the datasheet's C1/C2 (0.1 uF per supply pin); C5 adds the local
    # bulk the reference omits (this board hangs off 200 mm of ZH harness).
    for ref, x, val in (("C3", 236.22, "100nF"), ("C4", 243.84, "100nF"),
                        ("C5", 251.46, "1uF")):
        c = s.C(ref, x, 57.15, val)
        s.rail(c, "1", "+3V3", rise=2.54)
        s.gnd(c, "2", drop=2.54)

    # CAP (pin 9): internal regulator reservoir, 100 nF to GND (Fig. 1-6).
    C6 = s.C("C6", 293.37, 95.25, "100nF", rot=90)
    s.pw(U1, "9", ("x", 289.56))
    s.gnd(C6, "2", drop=2.54)

    # ---------------- 32.768 kHz clock ----------------
    # CLKSEL0 low + crystal on 26/27 = "Crystal" source (Fig. 1-8).  The
    # performance table (Fig. 6-14) is only specified for an external clock or
    # crystal, so the internal RC is not used.  Same ABS07 part as the main
    # board's RTC crystal: 12.5 pF CL, +/-20 ppm — CEVA asks for 50 ppm/12.5 pF.
    Y1 = s.comp("Y1", "Device:Crystal", 297.18, 81.28, value="32.768kHz",
                footprint="Crystal:Crystal_SMD_3215-2Pin_3.2x1.5mm", rot=90,
                refpos=(301.63, 70.49, "left"), valpos=(301.63, 73.66, "left"))
    s.pw(U1, "27", ("x", 290.83), ("y", 77.47), ("pin", Y1, "2"))
    s.pw(U1, "26", ("x", 290.83), ("y", 85.09), ("pin", Y1, "1"))
    C7 = s.C("C7", 308.61, 77.47, "22pF", rot=90)
    s.w((297.18, 77.47), (304.80, 77.47))
    s.gnd(C7, "2", drop=2.54, via=5.08)
    C8 = s.C("C8", 308.61, 85.09, "22pF", rot=90)
    s.w((297.18, 85.09), (304.80, 85.09))
    s.gnd(C8, "2", drop=2.54)

    # ---------------- host interface ----------------
    s.glabel(U1, "19", "I2C_SCL")
    s.glabel(U1, "20", "I2C_SDA")
    s.glabel(U1, "14", "SENSOR_INT")   # active low, push-pull (Fig. 6-3)
    s.glabel(U1, "17", "BNO_SA0")
    s.glabel(U1, "18", "BNO_CSN")
    s.glabel(U1, "11", "BNO_NRST")
    s.glabel(U1, "4",  "BNO_BOOTN")
    s.glabel(U1, "15", "BNO_ENV_SCL")
    s.glabel(U1, "16", "BNO_ENV_SDA")

    # PS1 = PS0 = 0 selects I2C (note 5); CLKSEL0 = 0 selects the crystal.
    for p in ("5", "6", "10"):
        s.pw(U1, p, ("x", 226.06))
    s.w((226.06, 105.41), (226.06, 118.11))
    s.power_at(226.06, 118.11, "GND")

    # reserved pins — datasheet Fig. 1-6 says no connect
    for p in ("1", "7", "8", "12", "13", "21", "22", "23", "24"):
        s.nc(U1, p)

    # ---------------- config straps ----------------
    Y = 149.86

    def pu(ref, x, val, net):
        """pull-up: rail -> R -> net label"""
        r = s.R(ref, x, Y, val)
        s.rail(r, "1", "+3V3", rise=2.54)
        s.glabel(r, "2", net)
        return r

    def pd(ref, x, val, net, cap=False):
        """pull-down / decoupler: net label -> part -> GND"""
        p = (s.C if cap else s.R)(ref, x, Y, val)
        s.glabel(p, "1", net)
        s.gnd(p, "2", drop=2.54)
        return p

    # SA0 (pin 17) sets the I2C address LSB: R3 fitted = 0x4A (the CEVA
    # reference's R3/R4 pair, same DNI convention).  Move to R4 for 0x4B.
    # 10k, NOT the reference's 0R (v0.2, REVIEW.md #1): fitting both halves
    # of the pair is the assembly slip this layout invites, and through 0R
    # that shorts the MAIN board's +3V3 to GND -- the rail this board is fed
    # from, on a daughterboard with no LED and no silk hint.  Through 10k the
    # same slip costs 330 uA, the clock still boots, and the part enumerates
    # at a wrong-but-visible address.  SA0 is a CMOS input sampled at reset
    # (§1.2.2.1): 10k gives >=3.29 V / <=1 mV against V_IH = 0.55*VDDIO
    # = 1.82 V, so the strap is just as unambiguous as a jumper.
    pu("R4", 161.29, "10k (DNP)", "BNO_SA0")
    pd("R3", 173.99, "10k", "BNO_SA0")
    # H_CSN (pin 18) is unused in I2C mode.  Fig. 1-11 leaves it open; we tie
    # it to the inactive level so no CMOS input floats on a battery product.
    pu("R5", 186.69, "10k", "BNO_CSN")
    # NRST: no host line is free on J7, so a 10k/100nF POR holds reset until
    # the rail is up — which also guarantees BOOTN/PS1/PS0/CLKSEL0 (all
    # sampled at reset) are settled first.
    pu("R6", 199.39, "10k", "BNO_NRST")
    pd("C9", 212.09, "100nF", "BNO_NRST", cap=True)
    # BOOTN high = normal boot; low at reset = DFU bootloader (note 4).
    pu("R7", 224.79, "10k", "BNO_BOOTN")
    # Secondary "environmental" I2C master bus: unused here, but note 8 says
    # it MUST be pulled up regardless because the SH-2 firmware probes it at
    # every reset.  Do not tie these to the host bus — the BNO085 is master.
    pu("R8", 237.49, "10k", "BNO_ENV_SCL")
    pu("R9", 250.19, "10k", "BNO_ENV_SDA")

    # test pads: ground BOOTN then pulse NRST to enter the DFU bootloader
    TP1 = s.comp("TP1", "Connector:TestPoint", 262.89, Y, value="NRST",
                 footprint="TestPoint:TestPoint_Pad_D1.0mm")
    s.glabel(TP1, "1", "BNO_NRST")
    TP2 = s.comp("TP2", "Connector:TestPoint", 275.59, Y, value="BOOTN",
                 footprint="TestPoint:TestPoint_Pad_D1.0mm")
    s.glabel(TP2, "1", "BNO_BOOTN")

    s.text("CONFIG STRAPS  (BNO_* nets join by name)", 155, 129, size=1.6, bold=True)
    s.text("Read the BNO085 only when SENSOR_INT is asserted: on a poll with no data ready it", 161.29, 172, size=1.3)
    s.text("STRETCHES SCL (§1.2.2.1) and would stall the whole shared bus (BME688/TSL2591/MCP23017).", 161.29, 176.5, size=1.3)

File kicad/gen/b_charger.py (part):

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    s.route(R10, "2", R11, "1", "V")
    s.pw(R11, "1", ("px", U2, "2"))          # lane y=93.98
    s.gnd(R11, "2", drop=0)
    # CHRG / FAULT open-drain -> pull-ups + labels (to MCP23017 GPB1/GPB2),
    # dropped below the pin lanes so the pull-ups sit in free space
    s.pw(U2, "4", ("x", 254.00), ("y", 116.84), ("x", 233.68))
    s.glabel_at("CHRG", 233.68, 116.84, 180)
    R12 = s.R("R12", 243.84, 113.03, "10k")
    s.rail(R12, "1", "+3V3", rise=0)
    s.pw(U2, "5", ("x", 256.54), ("y", 135.89), ("x", 243.84))
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    s.gnd(Q1, "2", drop=0)                               # source
    s.pw(Q1, "1", ("x", 320.04))                         # gate
    s.pw(Q1, "3", ("pin", R16, "2"))                     # drain -> R16 (976k); explicit + pin-relative so both follow moves
    s.glabel_at("FULLCHG_EN", 320.04, s.pxy(Q1, "1")[1], 180)  # label tracks Q1's gate y
    # gate pulldown: MCP23017 is hi-Z at POR -> without it the gate floats
    # and the 4.05 V "fixed in HW" charge cap isn't guaranteed at boot.
    # x=336.55 keeps its texts clear of Q1's "2N7002" value string.
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    s.pw(C110, "1", ("px", R22, "2"))
    s.gnd(C110, "2", drop=0)
    s.pw(R22, "2", ("x", 83.82))
    s.glabel_at("VBAT_SENSE", 83.82, 213.36, 180)
    # D13: Schottky clamp, cathode on the ADC node -- a REVERSED cell drives
    # the divider midpoint to ~-2 V; clamp at ~-0.2 V so the ESP32 pad stays
    # inside abs-max (100 k limits the current either way). BAT42W =
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    s.route(R23, "2", Q3, "3", "V")
    s.gnd(Q3, "2", drop=0)
    s.pw(Q3, "1", ("x", 81.28), ("y", 219.71), ("x", 78.74))  # gate -> node (R25 taps) -> up/over to the moved label
    s.glabel_at("VBAT_DIV_EN", 78.74, 219.71, 180)
    # gate pulldown (expander hi-Z at POR): divider defaults to disconnected
    R25 = s.R("R25", 67.31, 233.68, "100k",
              refpos=(66.29, 232.28, "right"), valpos=(66.29, 235.08, "right"))
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    s.pw(Q8, "3", ("py", R27, "2"))                           # drain joins node A
    s.gnd(Q8, "2", drop=0)
    s.pw(Q8, "1", ("x", 123.19))                              # gate run left
    s.glabel_at("CELL_TEST", 123.19, 190.50, 180)
    R26 = s.R("R26", 127.00, 194.31, "100k",                  # Q8 gate pulldown
              refpos=(125.73, 192.91, "right"), valpos=(125.73, 195.71, "right"))
    s.gnd(R26, "2", drop=0)
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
